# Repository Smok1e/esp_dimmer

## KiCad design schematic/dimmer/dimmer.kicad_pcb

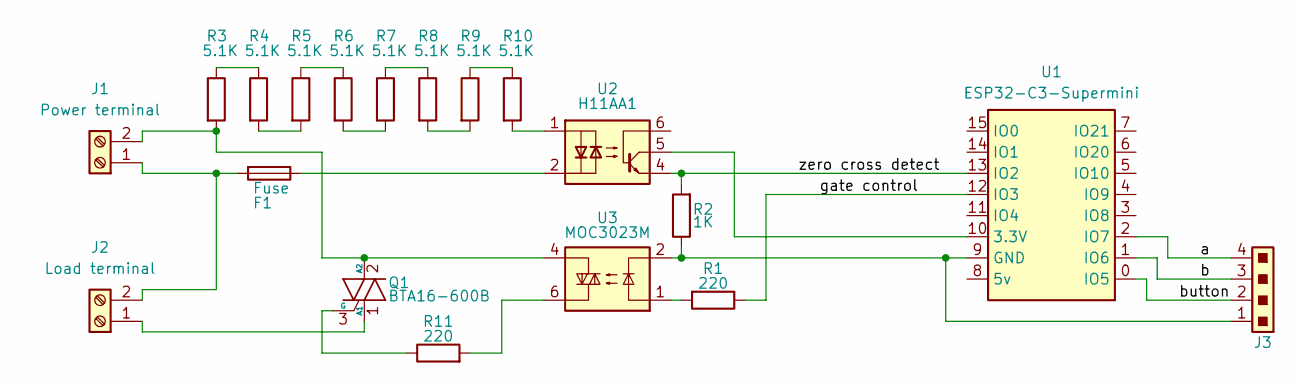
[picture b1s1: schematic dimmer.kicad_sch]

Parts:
F1: Fuse; Fuse_Littelfuse_395Series
J1: Power terminal; TerminalBlock_MaiXu_MX126-5.0-02P_1x02_P5.00mm
J2: Load terminal; TerminalBlock_MaiXu_MX126-5.0-02P_1x02_P5.00mm
J3: JST_Connector_4pin
Q1: BTA16-600B; TO-220-3_Vertical
R1, R11: 220; R_Axial_DIN0204_L3.6mm_D1.6mm_P7.62mm_Horizontal
R2: 1K; R_Axial_DIN0204_L3.6mm_D1.6mm_P7.62mm_Horizontal
R3, R4, R5, R6, R7, R8, R9, R10: 5.1K; R_Axial_DIN0204_L3.6mm_D1.6mm_P7.62mm_Horizontal
U1: ESP32-C3-Supermini
U2: H11AA1; DIP-6_W7.62mm_SMDSocket_SmallPads
U3: MOC3023M; DIP-6_W7.62mm

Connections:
/a: J3.4, U1.2 (IO7)
/b: J3.3, U1.1 (IO6)
/button: J3.2, U1.0 (IO5)
/gate control: R1.1, U1.12 (IO3)
/zero cross detect: R2.2, U1.13 (IO2), U2.4
unnamed: F1.1, U2.2
unnamed: F1.2, J1.1, J2.2
unnamed: J1.2, Q1.2 (A2), R3.2, U3.4
unnamed: J2.1, Q1.1 (A1)
unnamed: Q1.3 (G), R11.1
unnamed: R1.2, U3.1
unnamed: R3.1, R4.1
unnamed: R4.2, R5.2
unnamed: R5.1, R6.1
unnamed: R6.2, R7.2
unnamed: R7.1, R8.1
unnamed: R8.2, R9.2
unnamed: R9.1, R10.1
unnamed: R10.2, U2.1
unnamed: R11.2, U3.6
unnamed: J3.1, R2.1, U1.9 (GND), U3.2
unnamed: U1.10 (3.3V), U2.5

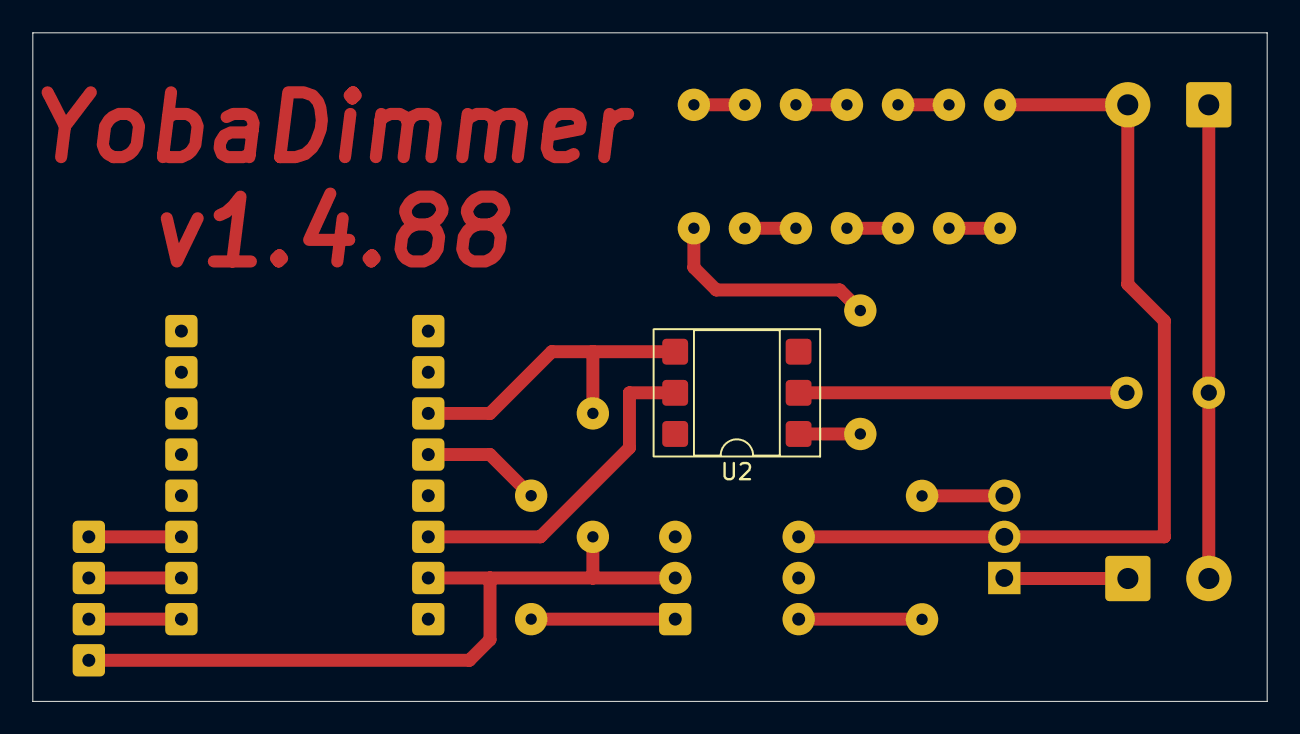
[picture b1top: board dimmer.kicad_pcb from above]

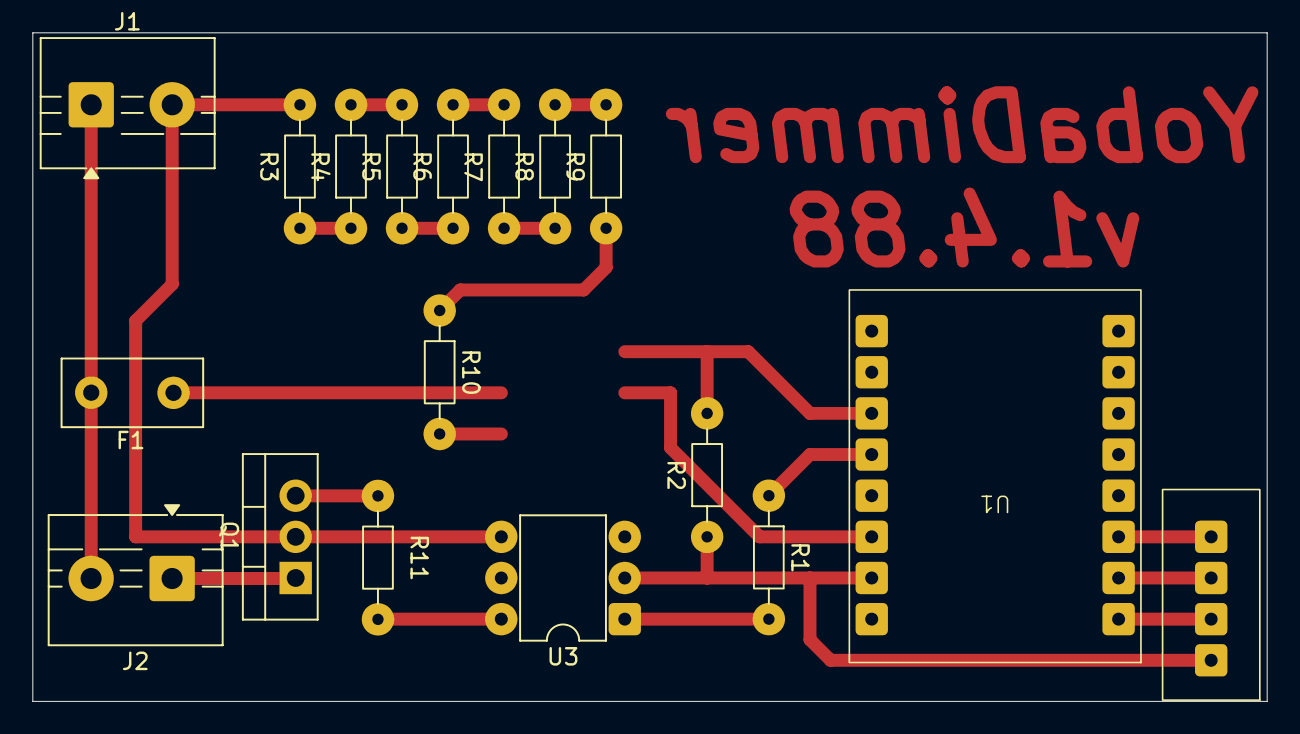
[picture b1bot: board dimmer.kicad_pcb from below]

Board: 2 copper layers, 76.2 x 41.3 mm, 19 parts (18 on the bottom side), 22 nets.
